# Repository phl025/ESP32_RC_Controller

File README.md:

# Arduino RC Controller for ESP32

## Description
This is a RC controller including engine sound player, PWM outputs for servos, ESC drivers and digital outputs.

## Details
It is based on *'Rc_Engine_Sound_ESP32'* : https://github.com/TheDIYGuy999/Rc_Engine_Sound_ESP32.

If you need to use it for trucks, cars, or other vehicles, it is easier to use the original version.

This version is modified for my boats.

## Software
Many functions are converted to 'object-oriented programming', such as :
- Receiver : RxBase, RxPpm, RxCrsf, RxSbus, RxPwm
- RX Channels : RxChannel, chTrigger
- ESC : escDriver for RZ7886 or IBT2
- ...

## Hardware
You can use the original hardware, but a modified version is available. 

Modifications : 
- Add pins for diagnostics or futures extensions.
- CH5, CH6 rename to IN1, IN2 (could be use for PWM input CH5, CH6 or 'motor encoder')
- Add input IN3, pin 39
- Add CH7, pin 15 (for steering servo in case of 3x ECS)

## PCB

See "hardware/pictures/"

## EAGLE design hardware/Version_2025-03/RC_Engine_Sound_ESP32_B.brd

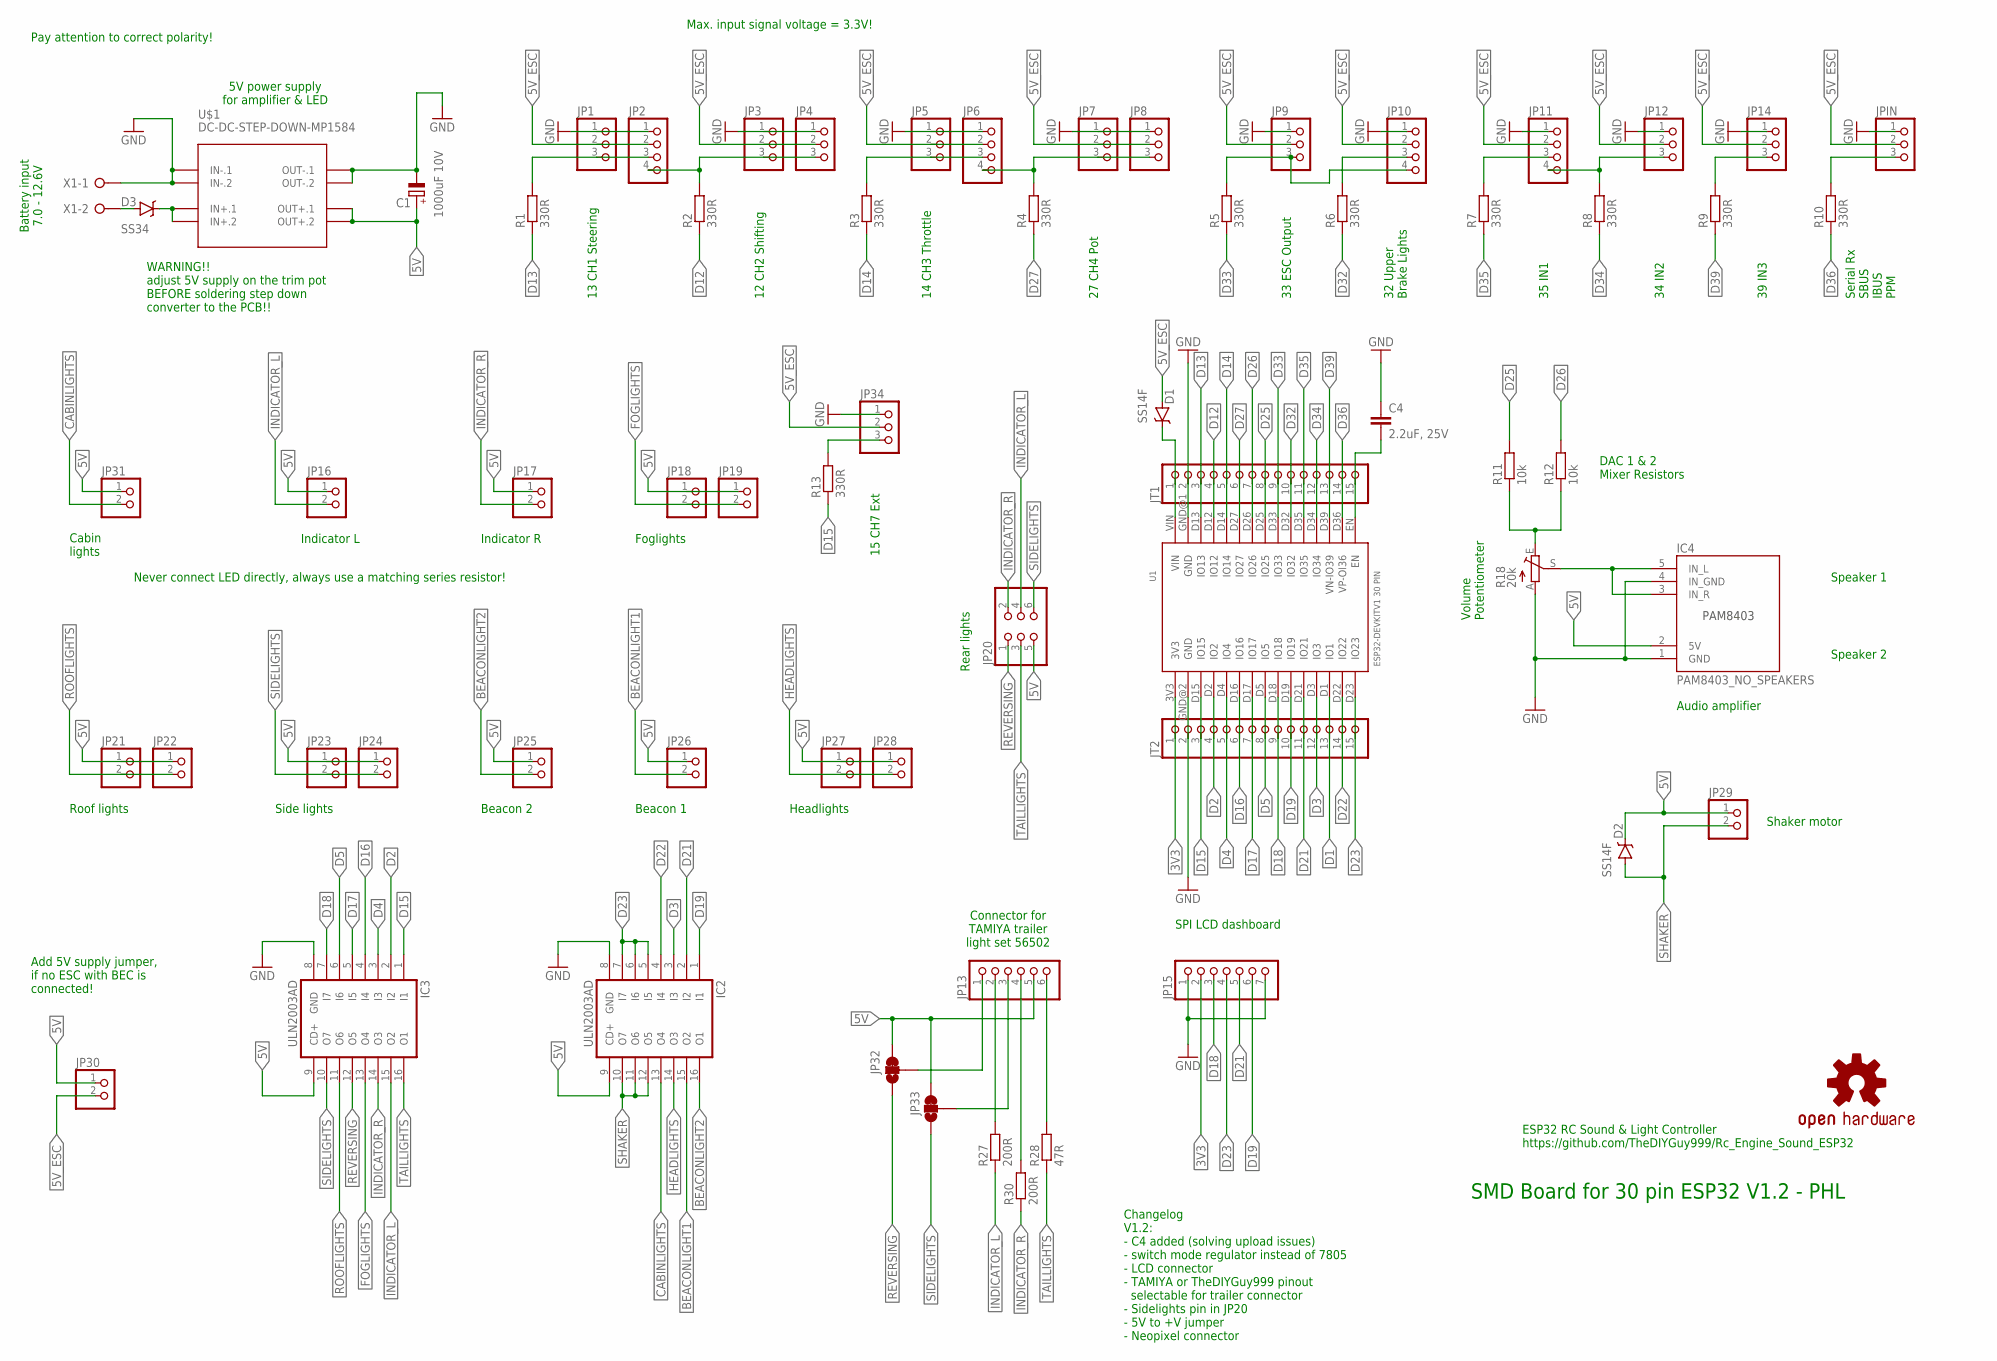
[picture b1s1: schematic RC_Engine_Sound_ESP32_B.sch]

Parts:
C1: 1000uF 10V; UD-10X10_NICHICON
C4: 2.2uF, 25V; C1206
D1, D2: SS14F; SMA-DIODE
D3: SS34; SMA-DIODE
IC2, IC3: ULN2003AD; SO16
IC4: PAM8403_NO_SPEAKERS
JP1, JP3, JP4, JP5, JP7, JP8, JP9, JP12, JP14, JP34: PINHD-1X3; 1X03
JP2, JP6, JP10, JP11: 00_CUSTOM_PINHEAD_PINHD-1X4; 00_CUSTOM_PINHEAD_1X04
JP13: PINHD-1X6; 1X06
JP15: PINHD-1X7; 1X07
JP16, JP17, JP18, JP19, JP21, JP22, JP23, JP24, JP25, JP26, JP27, JP28, JP29, JP30, JP31: PINHD-1X2; 1X02
JP20: PINHD-2X3; 2X03
JP32, JP33: JUMPER-PAD-3-2OF3_NC_BY_TRACE_LARGE; PAD-JUMPER-3-2OF3_NC_BY_TRACE_YES_SILK_LARGE
JPIN: PINHD-1X3; 1X03
JT1, JT2: 00_CUSTOM_PINHEAD_PINHD-1X15; 00_CUSTOM_PINHEAD_1X15
LOGO1: OSHW-LOGOM; OSHW-LOGO-M
R1, R2, R3, R4, R5, R6, R7, R8, R9, R10, R13: 330R; R0805
R11, R12: 10k; R0805
R18: 20k; S64W
R27, R30: 200R; R0805
R28: 47R; R0805
U1: ESP32DEVKITV1; ESP32-DEVKITV1
U$1: DC-DC-STEP-DOWN-MP1584
X1: W237-02P; W237-132

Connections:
3V3: JP15.2, JT2.1, U1.3V3
5V: C1.+, D2.C, IC2.9 (CD+), IC3.9 (CD+), IC4.2 (5V), JP13.5, JP16.1, JP17.1, JP18.1, JP19.1, JP20.5, JP21.1, JP22.1, JP23.1, JP24.1, JP25.1, JP26.1, JP27.1, JP28.1, JP29.1, JP30.1, JP31.1, JP32.3, JP33.3, U$1.OUT+.1, U$1.OUT+.2
5V_ESC: D1.A, JP1.2, JP2.2, JP3.2, JP4.2, JP5.2, JP6.2, JP7.2, JP8.2, JP9.2, JP10.2, JP11.2, JP12.2, JP14.2, JP30.2, JP34.2, JPIN.2
BEACONLIGHT1: IC2.15 (O2), JP26.2
BEACONLIGHT2: IC2.16 (O1), JP25.2
CABINLIGHTS: IC2.13 (O4), JP31.2
D1: JT2.13, U1.D1 (IO1)
D2: IC3.2 (I2), JT2.4, U1.D2 (IO2)
D3: IC2.3 (I3), JT2.12, U1.D3 (IO3)
D4: IC3.3 (I3), JT2.5, U1.D4 (IO4)
D5: IC3.6 (I6), JT2.8, U1.D5 (IO5)
D12: JT1.4, R2.1, U1.D12 (IO12)
D13: JT1.3, R1.1, U1.D13 (IO13)
D14: JT1.5, R3.1, U1.D14 (IO14)
D15: IC3.1 (I1), JT2.3, R13.1, U1.D15 (IO15)
D16: IC3.4 (I4), JT2.6, U1.D16 (IO16)
D17: IC3.5 (I5), JT2.7, U1.D17 (IO17)
D18: IC3.7 (I7), JP15.3, JT2.9, U1.D18 (IO18)
D19: IC2.1 (I1), JP15.6, JT2.10, U1.D19 (IO19)
D21: IC2.2 (I2), JP15.5, JT2.11, U1.D21 (IO21)
D22: IC2.4 (I4), JT2.14, U1.D22 (IO22)
D23: IC2.5 (I5), IC2.6 (I6), IC2.7 (I7), JP15.4, JT2.15, U1.D23 (IO23)
D25: JT1.8, R11.2, U1.D25 (IO25)
D26: JT1.7, R12.2, U1.D26 (IO26)
D27: JT1.6, R4.1, U1.D27 (IO27)
D32: JT1.10, R6.1, U1.D32 (IO32)
D33: JT1.9, R5.1, U1.D33 (IO33)
D34: JT1.12, R8.1, U1.D34 (IO34)
D35: JT1.11, R7.1, U1.D35 (IO35)
D36: JT1.14, R10.1, U1.D36 (VP-OI36)
D39: JT1.13, R9.1, U1.D39 (VN-IO39)
FOGLIGHTS: IC3.13 (O4), JP18.2, JP19.2
GND: C1.-, C4.1, IC2.8 (GND), IC3.8 (GND), IC4.1 (GND), IC4.4 (IN_GND), JP1.1, JP2.1, JP3.1, JP4.1, JP5.1, JP6.1, JP7.1, JP8.1, JP9.1, JP10.1, JP11.1, JP12.1, JP14.1, JP15.1, JP15.7, JP34.1, JPIN.1, JT1.2, JT2.2, R18.A, U1.GND@1 (GND), U1.GND@2 (GND), U$1.IN-.1, U$1.IN-.2, U$1.OUT-.1, U$1.OUT-.2, X1.1
HEADLIGHTS: IC2.14 (O3), JP27.2, JP28.2
INDICATOR_L: IC3.15 (O2), JP16.2, JP20.4, R27.1
INDICATOR_R: IC3.14 (O3), JP17.2, JP20.2, R30.1
unnamed: IC4.3 (IN_R), IC4.5 (IN_L), R18.S
unnamed: R11.1, R12.1, R18.E
unnamed: JP1.3, JP2.3, R1.2
unnamed: JP13.6, R28.2
unnamed: JP2.4, JP3.3, JP4.3, R2.2
unnamed: JP5.3, JP6.3, R3.2
unnamed: JP6.4, JP7.3, JP8.3, R4.2
unnamed: JP9.3, JP10.4, R5.2
unnamed: D1.C, JT1.1, U1.VIN
unnamed: JP10.3, R6.2
unnamed: JP11.3, R7.2
unnamed: JP11.4, JP12.3, R8.2
unnamed: JP13.4, R30.2
unnamed: JPIN.3, R10.2
unnamed: JP13.2, R27.2
unnamed: JP13.1, JP32.2
unnamed: C4.2, JT1.15, U1.EN
unnamed: JP13.3, JP33.2
unnamed: D3.C, U$1.IN+.1, U$1.IN+.2
unnamed: D3.A, X1.2
unnamed: JP14.3, R9.2
unnamed: JP34.3, R13.2
REVERSING: IC3.12 (O5), JP20.1, JP32.1
ROOFLIGHTS: IC3.11 (O6), JP21.2, JP22.2
SHAKER: D2.A, IC2.10 (O7), IC2.11 (O6), IC2.12 (O5), JP29.2
SIDELIGHTS: IC3.10 (O7), JP20.6, JP23.2, JP24.2, JP33.1
TAILLIGHTS: IC3.16 (O1), JP20.3, R28.1

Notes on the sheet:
Speaker 1
Speaker 2
13 CH1 Steering
12 CH2 Shifting
14 CH3 Throttle
27 CH4 Pot
33 ESC Output
32 Upper Brake Lights
35 IN1
34 IN2
Serial Rx SBUS IBUS PPM
DAC 1 & 2 Mixer Resistors
Audio amplifier
Volume Potentiometer
5V power supply for amplifier & LED
Battery input 7.0 - 12.6V
SMD Board for 30 pin ESP32 V1.2 - PHL
Shaker motor
Headlights
Foglights
Indicator L
Indicator R
Roof lights
Side lights
Connector for TAMIYA trailer light set 56502
Rear lights
ESP32 RC Sound & Light Controller https://github.com/TheDIYGuy999/Rc_Engine_Sound_ESP32
Never connect LED directly, always use a matching series resistor!
Beacon 2
Beacon 1
Cabin lights
Pay attention to correct polarity!
Max. input signal voltage = 3.3V!
Changelog V1.2: - C4 added (solving upload issues) - switch mode regulator instead of 7805 - LCD connector - TAMIYA or TheDIYGuy999 pinout selectable for trailer connector - Sidelights pin in JP20 - 5V to +V jumper - Neopixel connector
WARNING!! adjust 5V supply on the trim pot BEFORE soldering step down converter to the PCB!!
SPI LCD dashboard
Add 5V supply jumper, if no ESC with BEC is connected!
39 IN3
15 CH7 Ext

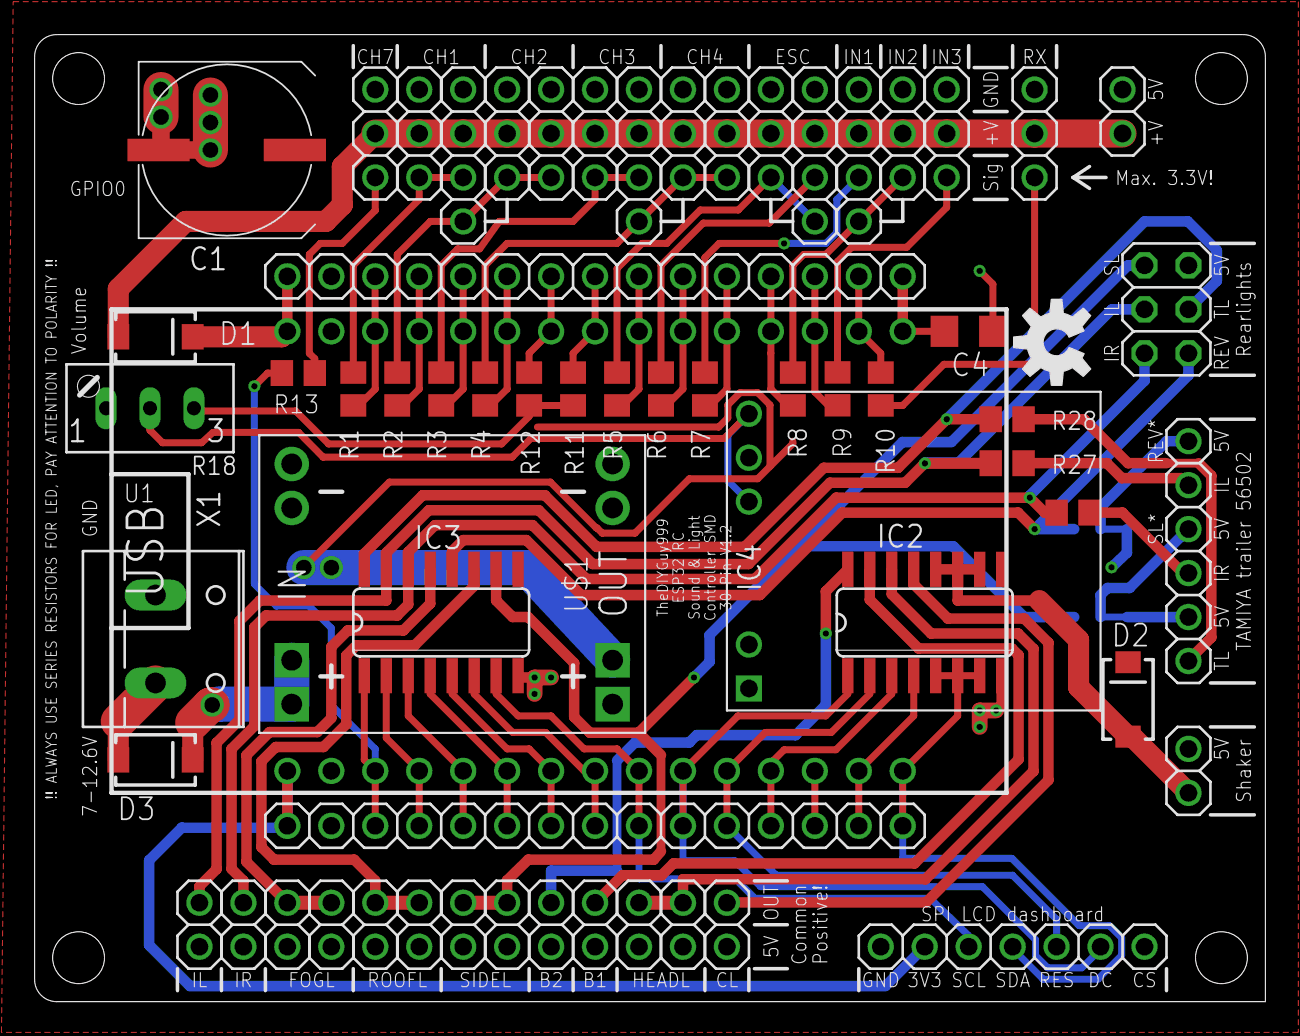
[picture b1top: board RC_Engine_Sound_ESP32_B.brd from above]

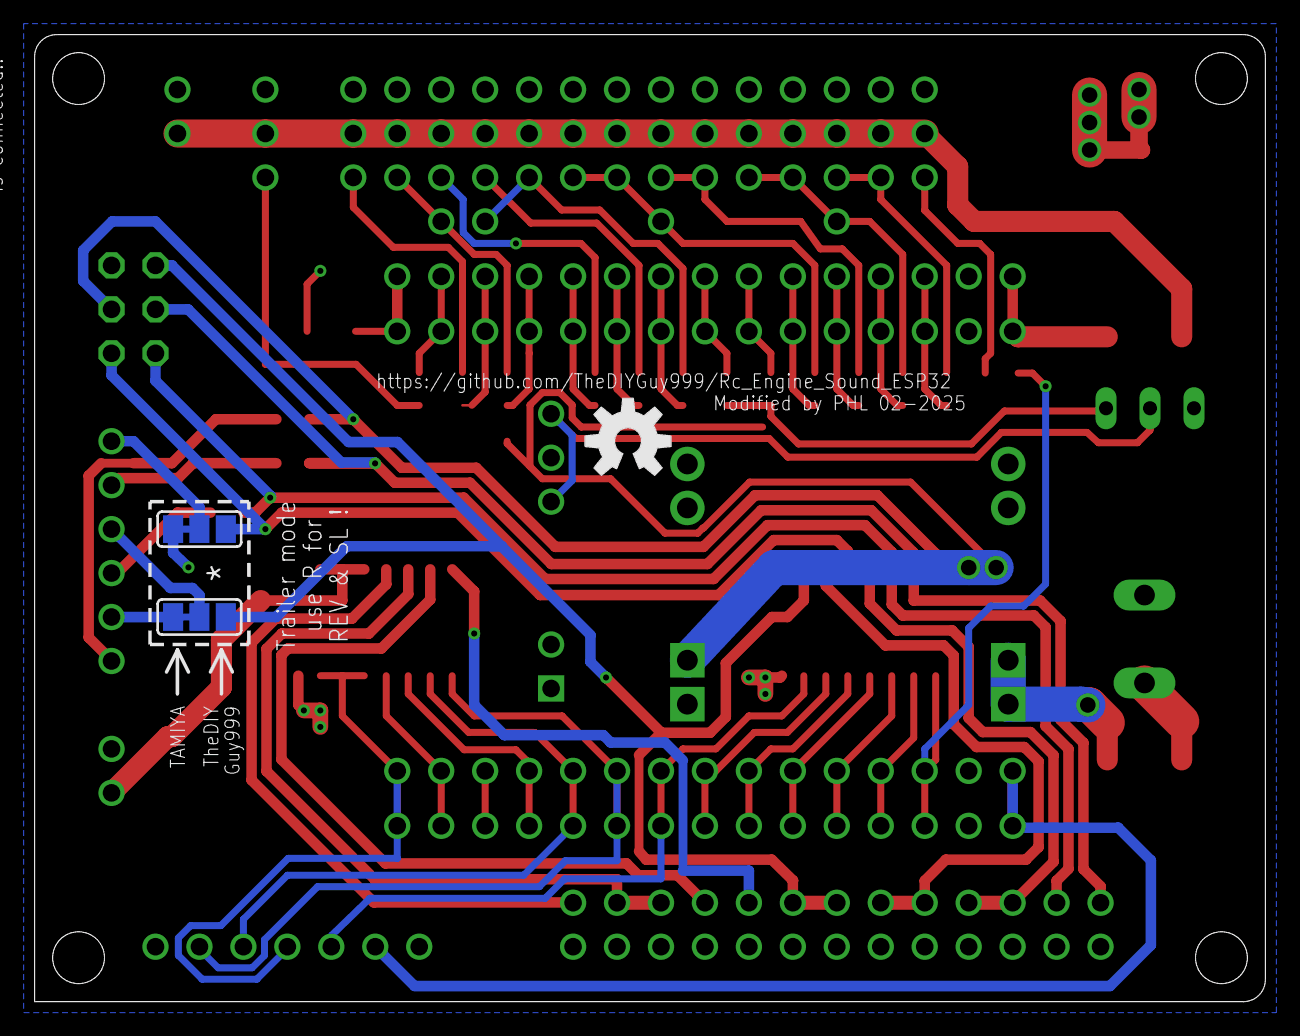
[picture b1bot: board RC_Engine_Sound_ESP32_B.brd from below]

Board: 2 copper layers, 71.1 x 55.9 mm, 67 parts (3 on the bottom side), 63 nets.

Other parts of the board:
LOGO2: OSHW-LOGOM; OSHW-LOGO-M

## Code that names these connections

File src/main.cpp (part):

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#if defined STD_DASHBOARD or defined FREVIC_DASHBOARD or defined NAVY_DASHBOARD
	// Dashboard setup
	Serial.printf("* Setup DASHBOARD :\n");
	Serial.printf("* - Pins 18 (sidelights), 19 (beacon2), 21 (beacon1), 23 (shaker) are not usable for Outputs !\n");
	//Serial.printf("-------------------------------------\n");
	dashboard.init(TFT_ROTATION);	//(dashRotation);
	//dashboard.init(3);	//(dashRotation);
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	// static uint32_t curSirenSample = 0;							  // Index of currently loaded siren sample
	// static uint32_t curSound1Sample = 0;						  // Index of currently loaded sound1 sample
	// static uint32_t curSound2Sample = 0;						  // Index of currently loaded sound2 sample - Add PHL
	// static uint32_t curReversingSample = 0;						  // Index of currently loaded reversing beep sample
	// static uint32_t curIndicatorSample = 0;						  // Index of currently loaded indicator tick sample
	// static uint32_t curWastegateSample = 0;						  // Index of currently loaded wastegate sample
	// static uint32_t curBrakeSample = 0;							  // Index of currently loaded brake sound sample
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	static uint32_t curHornSample = 0;							  // Index of currently loaded horn sample
	static uint32_t curSirenSample = 0;							  // Index of currently loaded siren sample
	static uint32_t curSound1Sample = 0;						  // Index of currently loaded sound1 sample
	static uint32_t curReversingSample = 0;						  // Index of currently loaded reversing beep sample
	static uint32_t curIndicatorSample = 0;						  // Index of currently loaded indicator tick sample
	static uint32_t curWastegateSample = 0;						  // Index of currently loaded wastegate sample
	static uint32_t curBrakeSample = 0;							  // Index of currently loaded brake sound sample
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
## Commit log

2025-11-09 Initial version 0.1
2025-11-10 Fix spelling and improve README description
    Updated README to correct spelling and enhance clarity.
2025-11-24 Test PPM mode, NOT stable for integrator (MC2010, Trainer output)
2025-12-18 Add badges for latest release and download count
2026-01-27 Refactor RxChannel class and related files for improved functionality and clarity
    - Added binary value to RxChannel for CRSF/SBUS communication.
    - Introduced switchBits_ and switchLatchs_ for multiswitch handling.
    - Updated process method to include failsafe handling and improved integrator logic.
    - Implemented GetMix4 and GetMix3P methods for multiswitch state retrieval.
    - Adjusted CRSF protocol definitions for channel value mapping.
    - Removed unused rcTrigger and statusLED classes to streamline codebase.
2026-03-02 Add TFT dashboard support; ESC ramp param
    Introduce TFT dashboard support and related assets (DIYGuy999 std and Frevic)
2026-05-11 Add navy dashbord, update outputs.

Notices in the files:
parts and their libraries:
SparkFun-Aesthetics: Licensing: Creative Commons ShareAlike 4.0 International - https://creativecommons.org/licenses/by-sa/4.0
